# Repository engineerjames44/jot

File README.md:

# Jot

A voice-first personal hub for iOS 26. Hold the mic button, speak, and Jot turns
it into a note, task, reminder, or calendar event.

## Pipeline

```
AudioSource (MicAudioSource; BLE later)
  → SpeechTranscription (SpeechAnalyzer, on-device)
  → OnDeviceClassifier (Apple Foundation Models, default)
    or ProxyClassifier (Claude Haiku 4.5 via jamescronin.dev/api/jot/classify, opt-in)
  → JotItem (SwiftData)
  → ReminderScheduler (local notifications, soonest 64)
```

| Folder | What's there |
| --- | --- |
| `Jot/Audio` | `AudioSource` protocol and the mic implementation |
| `Jot/Speech` | On-device transcription and format conversion |
| `Jot/AI` | Sorting: on-device classifier (default), the jamescronin.dev proxy for Claude (opt-in), prompts and parsing |
| `Jot/Model` | `JotItem` SwiftData model |
| `Jot/Services` | Capture loop, Keychain, notifications, EventKit (read-only) |
| `Jot/Views` | Today, Inbox, item detail, Settings, record button |

### Adding the BLE source

Implement `AudioSource` (return an `AsyncStream<AudioChunk>` of PCM buffers in any
format, finish it on `stop()`) and pass it to `CaptureController(source:)` in
`JotApp`. Transcription converts to the analyzer's format itself.

## Targets

| Target | What it is |
| --- | --- |
| `Jot` | The app |
| `JotWidgets` | Home/Lock Screen widgets, the Control Center control, and the capture Live Activity |

`Shared/` is compiled into both: the SwiftData model, design system, brand colors,
the App Group store, Live Activity attributes, and the record intent. Both targets
use the App Group `group.com.jamescronin.Jot` so they read the same items.

## Develop tab (change notes)

A tab for noting changes to Jot itself as you use it. Tap the orb to record (tap
again to save); the words are kept exactly as said (no Claude), along with the
recording, the screen you were on, and the app version. **Shake the phone
anywhere** to record a note tagged with the current screen. **Export PDF** or
**Export TXT** makes a file of every note (open ones grouped into Bugs, Changes,
and Ideas, then Done) and opens the share sheet: Save to Files, AirDrop, Mail, and so on.

On by default in Debug builds, off in Release; toggle it in Settings › Developer.

## Setup

1. Open `Jot.xcodeproj` in Xcode 26.
2. Pick your team under Signing & Capabilities (and change the bundle ID if needed).
3. Run on a device or simulator. Sorting works out of the box on Apple's on-device model.
   Claude sorting is an opt-in under **Settings**; it goes through the jamescronin.dev proxy,
   which holds the API key, so Release builds never hold a key. Debug builds also accept a personal
   Claude key in Settings (Keychain only) for experiments, which calls Claude directly.

For UI work, launch a Debug build with the argument `-JotSampleData YES`
(Edit Scheme › Run › Arguments) to fill an empty store with a sample day and sample change notes.

The first recording downloads the on-device speech model for your language.
If sorting fails (model unavailable, offline), the transcript is saved as a note and sorted later, so nothing is lost.

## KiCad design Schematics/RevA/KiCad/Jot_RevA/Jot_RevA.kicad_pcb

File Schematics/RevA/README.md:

# Jot Rev A

First custom PCB: handheld push-to-talk voice capture with BLE sync to the iPhone app.
Architecture: [JOT-HW-001](Architecture/JOT-HW-001_Hardware_Architecture.pdf).

| Folder | What goes there |
| --- | --- |
| `Architecture/` | JOT-HW-001 and other design documents (pin map, power budget) |
| `Datasheets/` | Part datasheets, grouped by block from JOT-HW-001 section 4 |
| `KiCad/` | The KiCad project: schematic, PCB, project-local symbols and footprints |
| `BOM/` | Bill of materials exported from KiCad, with LCSC part numbers |
| `Fabrication/` | Gerbers, drill files, and assembly files sent to the board house |

## Datasheets by block

| Folder | Parts |
| --- | --- |
| `Power/` | USB-C connector and ESD, MCP73831 charger, TPS7A02 LDO, MAX17048, JST-PH, battery |
| `MCU/` | Raytac MDBT50Q-1MV2, nRF52840 Product Specification, 32.768 kHz crystal |
| `Audio/` | TDK T3902 PDM microphone, AO3401A mic power switch |
| `Storage/` | 128 MB QSPI NOR flash |
| `Sensors/` | LIS2DW12 accelerometer, DRV2605L haptic driver, LRA |
| `UI/` | Button, RGB LED, Rec LED, charge LED, buzzer, AO3400A, 1N4148W |
| `NFC/` | NFC antenna design notes and tuning references |
| `Passives/` | Samsung CL05/CL10 capacitor and UNI-ROYAL resistor series datasheets |

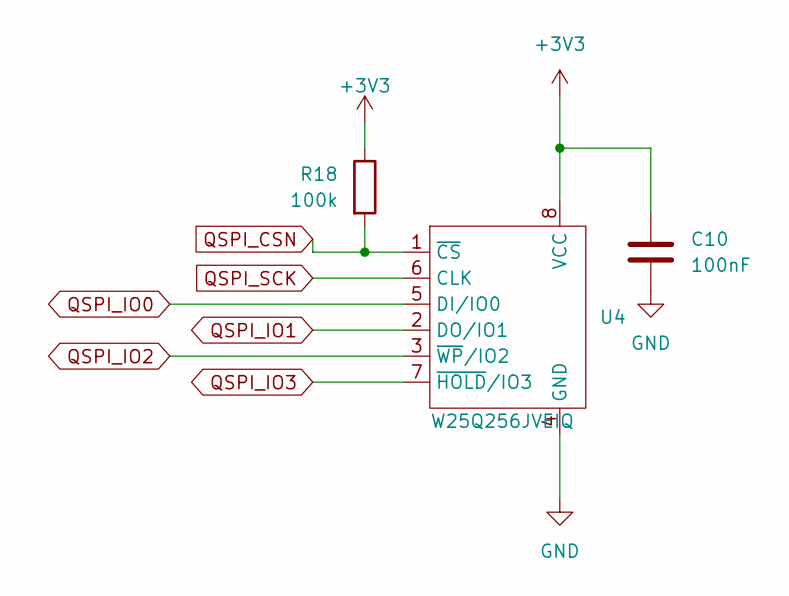
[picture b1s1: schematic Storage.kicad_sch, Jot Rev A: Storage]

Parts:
C10: 100nF; C_0402_1005Metric
R18: 100k; R_0402_1005Metric
U4: W25Q256JVEIQ; WSON-8-1EP_8x6mm_P1.27mm_EP3.4x4.3mm

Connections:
+3V3: C10.1, R18.1, U4.8 (VCC); also elsewhere on the board
GND: C10.2, U4.4 (GND); also elsewhere on the board
QSPI_CSN: R18.2, U4.1 (~CS); also elsewhere on the board
QSPI_IO0: U4.5 (DI/IO0); also elsewhere on the board
QSPI_IO1: U4.2 (DO/IO1); also elsewhere on the board
QSPI_IO2: U4.3 (~WP/IO2); also elsewhere on the board
QSPI_IO3: U4.7 (~HOLD/IO3); also elsewhere on the board
QSPI_SCK: U4.6 (CLK); also elsewhere on the board

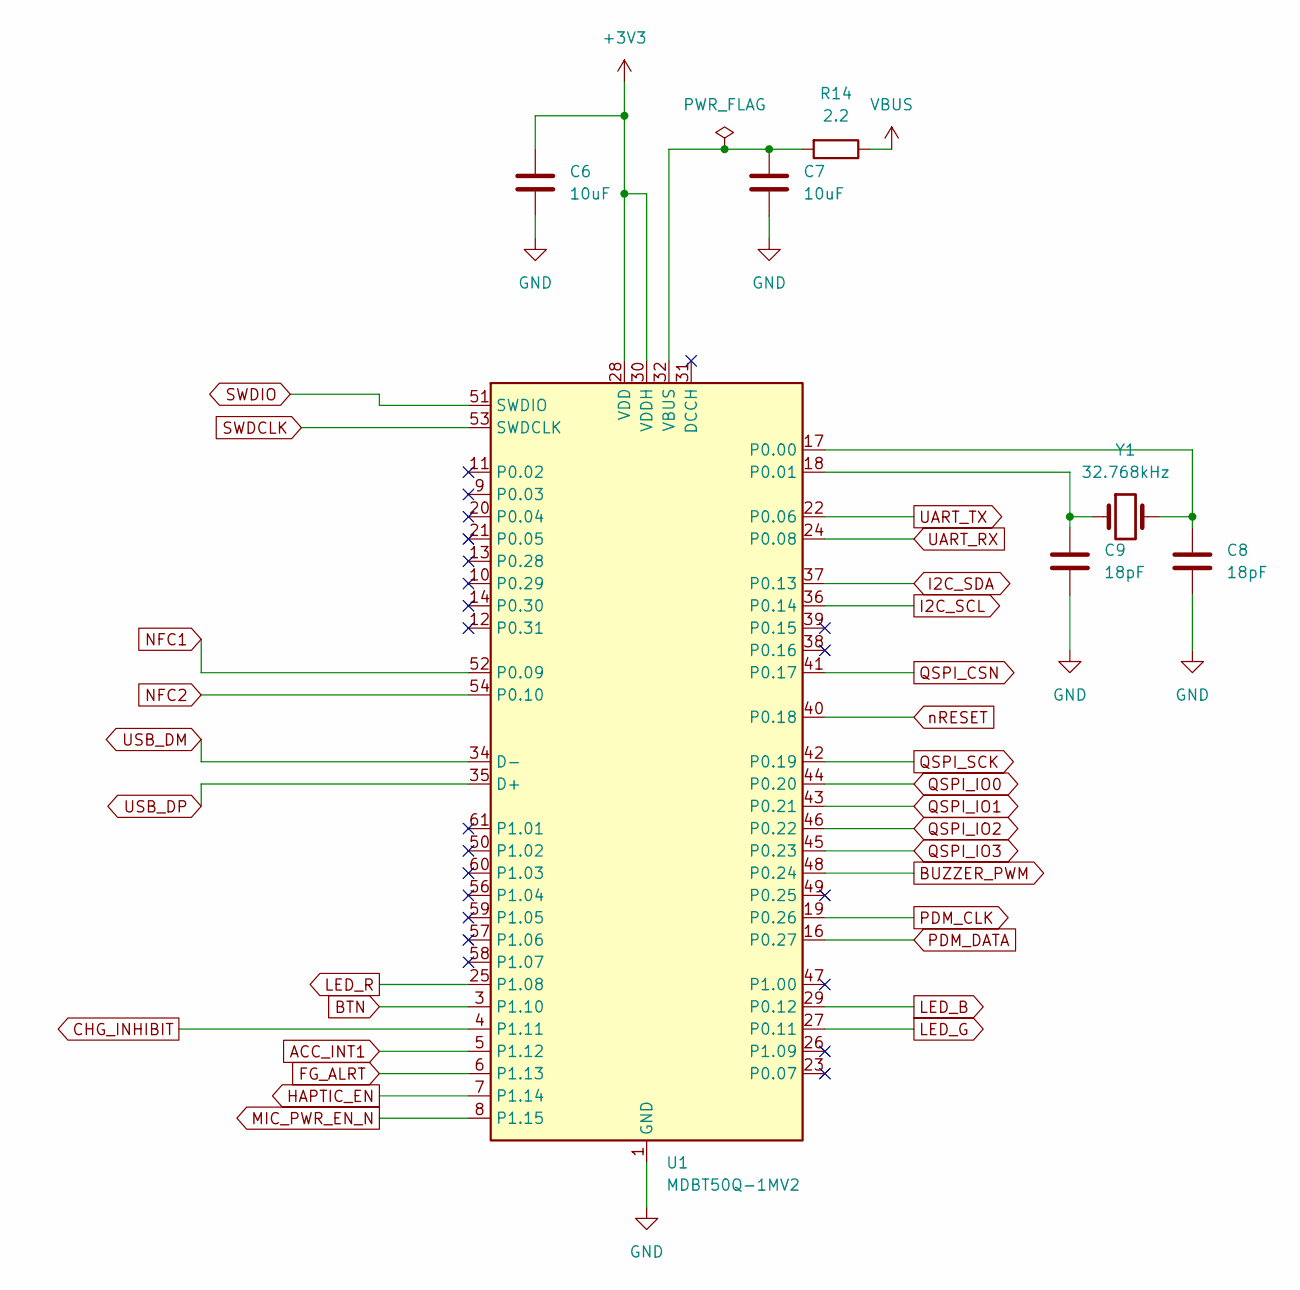
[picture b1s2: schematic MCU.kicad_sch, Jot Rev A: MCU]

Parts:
C6, C7: 10uF; C_0603_1608Metric
C8, C9: 18pF; C_0402_1005Metric
R14: 2.2; R_0402_1005Metric
U1: MDBT50Q-1MV2; Raytac_MDBT50Q
Y1: 32.768kHz; Crystal_SMD_3215-2Pin_3.2x1.5mm

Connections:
+3V3: C6.1, U1.28 (VDD), U1.30 (VDDH); also elsewhere on the board
ACC_INT1: U1.5 (P1.12); also elsewhere on the board
BTN: U1.3 (P1.10); also elsewhere on the board
BUZZER_PWM: U1.48 (P0.24); also elsewhere on the board
CHG_INHIBIT: U1.4 (P1.11); also elsewhere on the board
FG_ALRT: U1.6 (P1.13); also elsewhere on the board
GND: C6.2, C7.2, C8.2, C9.2, U1.1 (GND), U1.2 (GND), U1.15 (GND), U1.33 (GND), U1.55 (GND); also elsewhere on the board
HAPTIC_EN: U1.7 (P1.14); also elsewhere on the board
I2C_SCL: U1.36 (P0.14); also elsewhere on the board
I2C_SDA: U1.37 (P0.13); also elsewhere on the board
LED_B: U1.29 (P0.12); also elsewhere on the board
LED_G: U1.27 (P0.11); also elsewhere on the board
LED_R: U1.25 (P1.08); also elsewhere on the board
MIC_PWR_EN_N: U1.8 (P1.15); also elsewhere on the board
NFC1: U1.52 (P0.09); also elsewhere on the board
NFC2: U1.54 (P0.10); also elsewhere on the board
unnamed: C8.1, U1.17 (P0.00), Y1.2
unnamed: C9.1, U1.18 (P0.01), Y1.1
unnamed: C7.1, R14.2, U1.32 (VBUS)
PDM_CLK: U1.19 (P0.26); also elsewhere on the board
PDM_DATA: U1.16 (P0.27); also elsewhere on the board
QSPI_CSN: U1.41 (P0.17); also elsewhere on the board
QSPI_IO0: U1.44 (P0.20); also elsewhere on the board
QSPI_IO1: U1.43 (P0.21); also elsewhere on the board
QSPI_IO2: U1.46 (P0.22); also elsewhere on the board
QSPI_IO3: U1.45 (P0.23); also elsewhere on the board
QSPI_SCK: U1.42 (P0.19); also elsewhere on the board
SWDCLK: U1.53 (SWDCLK); also elsewhere on the board
SWDIO: U1.51 (SWDIO); also elsewhere on the board
UART_RX: U1.24 (P0.08); also elsewhere on the board
UART_TX: U1.22 (P0.06); also elsewhere on the board
USB_DM: U1.34 (D-); also elsewhere on the board
USB_DP: U1.35 (D+); also elsewhere on the board
VBUS: R14.1; also elsewhere on the board
nRESET: U1.40 (P0.18); also elsewhere on the board

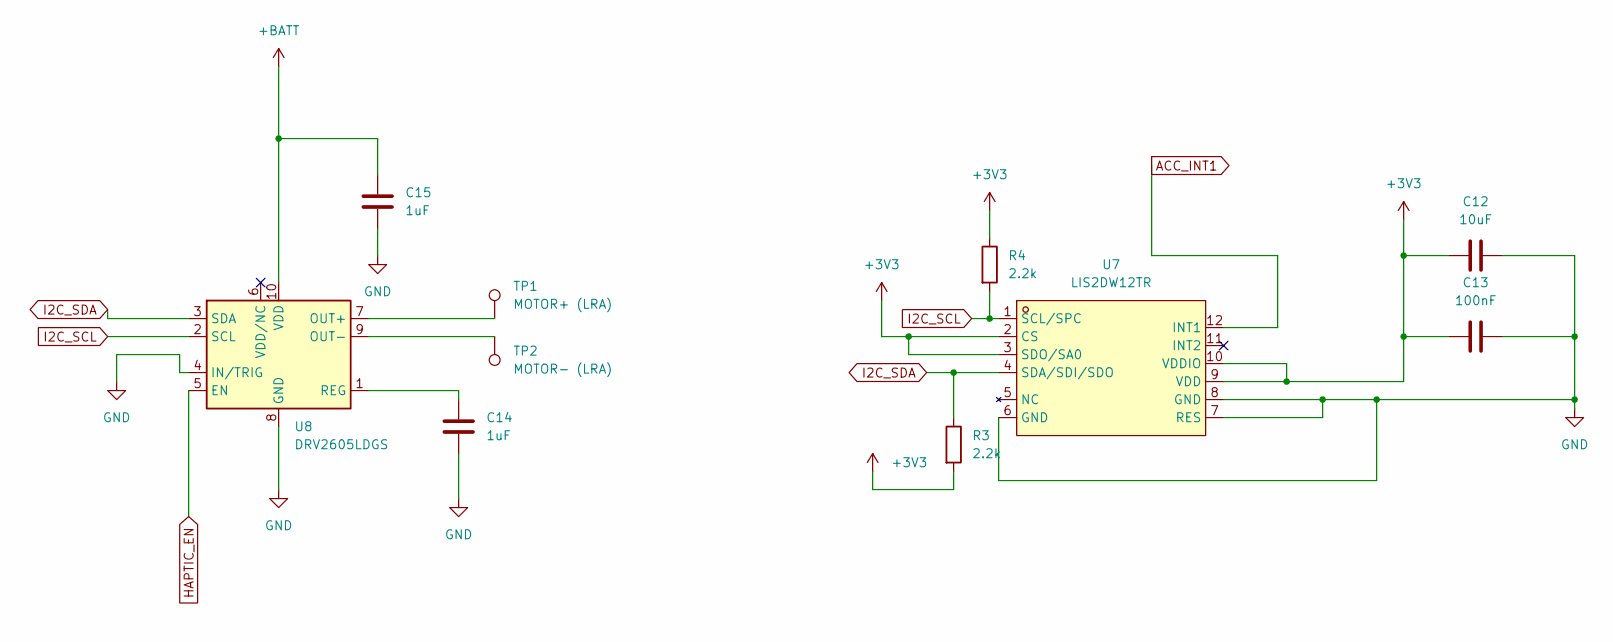
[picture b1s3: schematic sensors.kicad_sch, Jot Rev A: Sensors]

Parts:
C12: 10uF; C_0603_1608Metric
C13: 100nF; C_0402_1005Metric
C14, C15: 1uF; C_0402_1005Metric
R3, R4: 2.2k; R_0402_1005Metric
TP1: MOTOR+ (LRA); TestPoint_Pad_D2.0mm
TP2: MOTOR- (LRA); TestPoint_Pad_D2.0mm
U7: LIS2DW12TR; LGA-12_2x2mm_P0.5mm; MPN LIS2DW12TR; LCSC Part C189624
U8: DRV2605LDGS; TSSOP-10_3x3mm_P0.5mm

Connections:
+3V3: C12.2, C13.2, R3.2, R4.1, U7.2 (CS), U7.3 (SDO/SA0), U7.9 (VDD), U7.10 (VDDIO); also elsewhere on the board
+BATT: C15.1, U8.10 (VDD); also elsewhere on the board
ACC_INT1: U7.12 (INT1); also elsewhere on the board
GND: C12.1, C13.1, C14.2, C15.2, U7.6 (GND), U7.7 (RES), U7.8 (GND), U8.4 (IN/TRIG), U8.8 (GND); also elsewhere on the board
HAPTIC_EN: U8.5 (EN); also elsewhere on the board
I2C_SCL: R4.2, U7.1 (SCL/SPC), U8.2 (SCL); also elsewhere on the board
I2C_SDA: R3.1, U7.4 (SDA/SDI/SDO), U8.3 (SDA); also elsewhere on the board
unnamed: TP1.1 (1_1), U8.7 (OUT+)
unnamed: TP2.1 (1_1), U8.9 (OUT-)
unnamed: C14.1, U8.1 (REG)

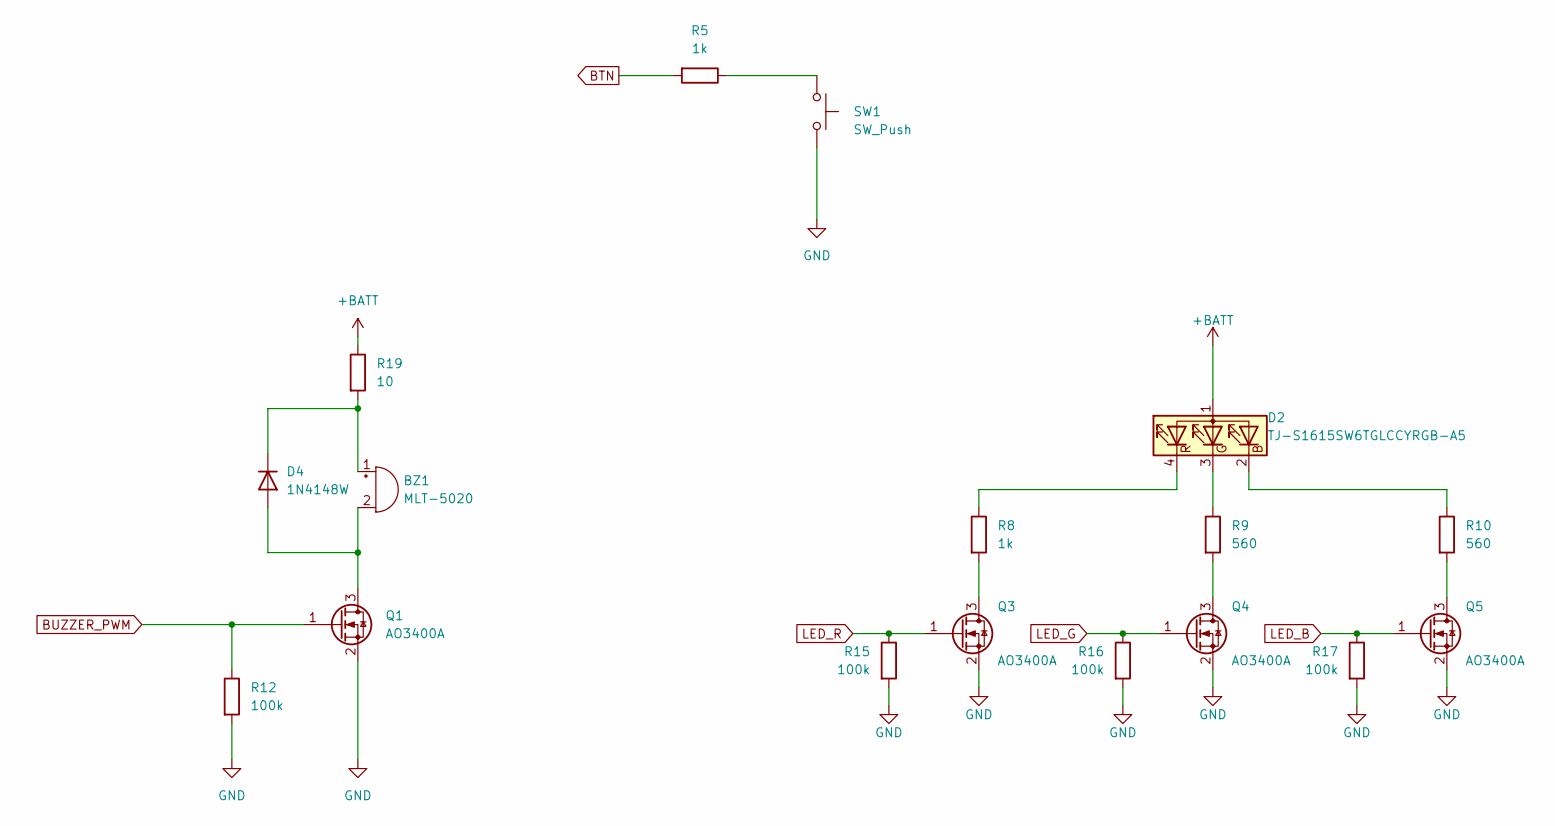
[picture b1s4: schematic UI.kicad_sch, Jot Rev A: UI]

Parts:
BZ1: MLT-5020; BUZ-SMD_L5.0-W5.5-P4.60
D2: TJ-S1615SW6TGLCCYRGB-A5; LED_RGB_TOGIALED_1615_1.6x1.5mm
D4: 1N4148W; D_SOD-123
Q1, Q3, Q4, Q5: AO3400A; SOT-23
R5, R8: 1k; R_0402_1005Metric
R9, R10: 560; R_0402_1005Metric
R12, R15, R16, R17: 100k; R_0402_1005Metric
R19: 10; R_2512_6332Metric
SW1: SW_Push; KEY-SMD_TX-1010-X-X

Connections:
+BATT: D2.1 (A), R19.1; also elsewhere on the board
BTN: R5.2; also elsewhere on the board
BUZZER_PWM: Q1.1 (G), R12.1; also elsewhere on the board
GND: Q1.2 (S), Q3.2 (S), Q4.2 (S), Q5.2 (S), R12.2, R15.2, R16.2, R17.2, SW1.2; also elsewhere on the board
LED_B: Q5.1 (G), R17.1; also elsewhere on the board
LED_G: Q4.1 (G), R16.1; also elsewhere on the board
LED_R: Q3.1 (G), R15.1; also elsewhere on the board
unnamed: BZ1.1 (+), D4.1 (K), R19.2
unnamed: BZ1.2 (-), D4.2 (A), Q1.3 (D)
unnamed: D2.2 (BK), R10.1
unnamed: D2.3 (GK), R9.1
unnamed: D2.4 (RK), R8.1
unnamed: Q3.3 (D), R8.2
unnamed: Q4.3 (D), R9.2
unnamed: Q5.3 (D), R10.2
unnamed: R5.1, SW1.1

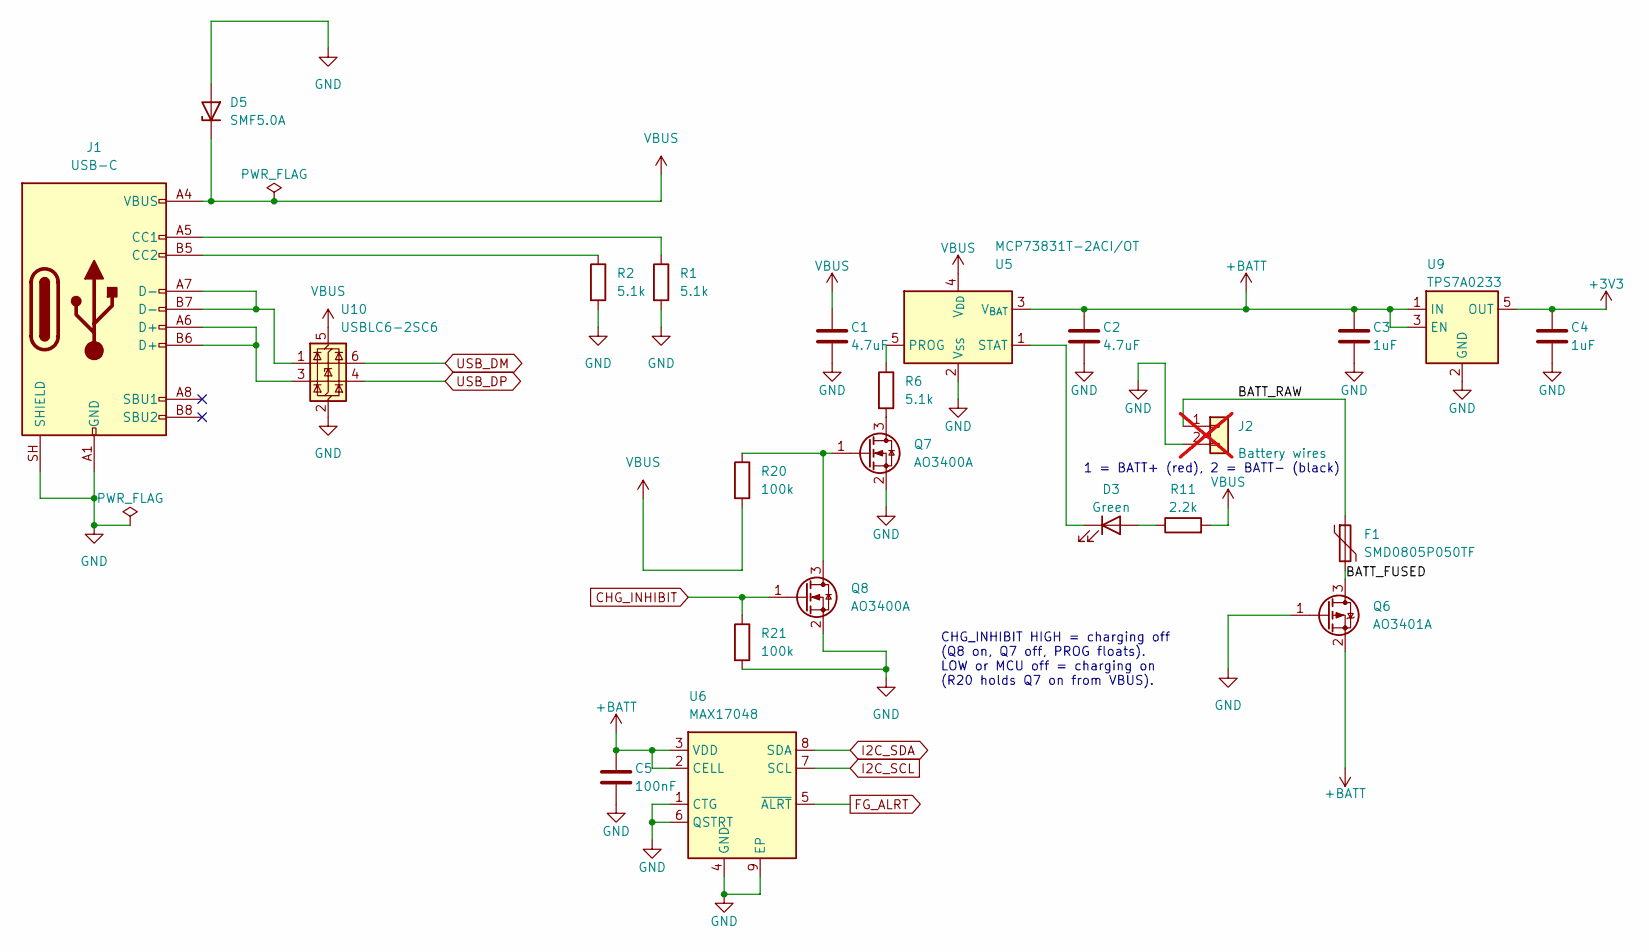
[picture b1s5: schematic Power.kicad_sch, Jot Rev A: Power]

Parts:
C1, C2: 4.7uF; C_0402_1005Metric
C3, C4: 1uF; C_0402_1005Metric
C5: 100nF; C_0402_1005Metric
D3: Green; LED_0603_1608Metric; LCSC C7429914
D5: SMF5.0A; D_SOD-123F
F1: SMD0805P050TF; Fuse_0805_2012Metric
J1: USB-C; USB_C_Receptacle_HRO_TYPE-C-31-M-12
J2: Battery wires; SolderWire-0.15sqmm_1x02_P4mm_D0.5mm_OD1.5mm; not fitted
Q6: AO3401A; SOT-23
Q7, Q8: AO3400A; SOT-23
R1, R2, R6: 5.1k; R_0402_1005Metric
R11: 2.2k; R_0402_1005Metric; LCSC C25879
R20, R21: 100k; R_0402_1005Metric
U5: MCP73831T-2ACI/OT; SOT-23-5
U6: MAX17048; DFN-8-1EP_2x2mm_P0.5mm_EP0.9x1.3mm; LCSC C2682616
U9: TPS7A0233; SOT-23-5; LCSC C2887324
U10: USBLC6-2SC6; SOT-23-6

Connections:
+3V3: C4.1, U9.5 (OUT); also elsewhere on the board
+BATT: C2.1, C3.1, C5.1, Q6.2 (S), U5.3 (V_{BAT}), U6.2 (CELL), U6.3 (VDD), U9.1 (IN), U9.3 (EN); also elsewhere on the board
/Power/BATT_FUSED: F1.2, Q6.3 (D)
/Power/BATT_RAW: F1.1, J2.1
CHG_INHIBIT: Q8.1 (G), R21.1; also elsewhere on the board
FG_ALRT: U6.5 (~ALRT); also elsewhere on the board
GND: C1.2, C2.2, C3.2, C4.2, C5.2, D5.2 (A), J1.A1 (GND), J1.A12 (GND), J1.B1 (GND), J1.B12 (GND), J1.SH (SHIELD), J2.2, Q6.1 (G), Q7.2 (S), Q8.2 (S), R1.2, R2.2, R21.2, U5.2 (V_{SS}), U6.1 (CTG), U6.4 (GND), U6.6 (QSTRT), U6.9 (EP), U9.2 (GND), U10.2 (GND); also elsewhere on the board
I2C_SCL: U6.7 (SCL); also elsewhere on the board
I2C_SDA: U6.8 (SDA); also elsewhere on the board
unnamed: D3.2 (A), R11.1
unnamed: D3.1 (K), U5.1 (STAT)
unnamed: J1.A5 (CC1), R1.1
unnamed: J1.B5 (CC2), R2.1
unnamed: J1.A6 (D+), J1.B6 (D+), U10.3 (I/O2)
unnamed: J1.A7 (D-), J1.B7 (D-), U10.1 (I/O1)
unnamed: Q7.3 (D), R6.2
unnamed: Q7.1 (G), Q8.3 (D), R20.1
unnamed: R6.1, U5.5 (PROG)
USB_DM: U10.6 (I/O1); also elsewhere on the board
USB_DP: U10.4 (I/O2); also elsewhere on the board
VBUS: C1.1, D5.1 (K), J1.A4 (VBUS), J1.A9 (VBUS), J1.B4 (VBUS), J1.B9 (VBUS), R11.2, R20.2, U5.4 (V_{DD}), U10.5 (VBUS); also elsewhere on the board

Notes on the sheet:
CHG_INHIBIT HIGH = charging off (Q8 on, Q7 off, PROG floats). LOW or MCU off = charging on (R20 holds Q7 on from VBUS).
1 = BATT+ (red), 2 = BATT− (black)

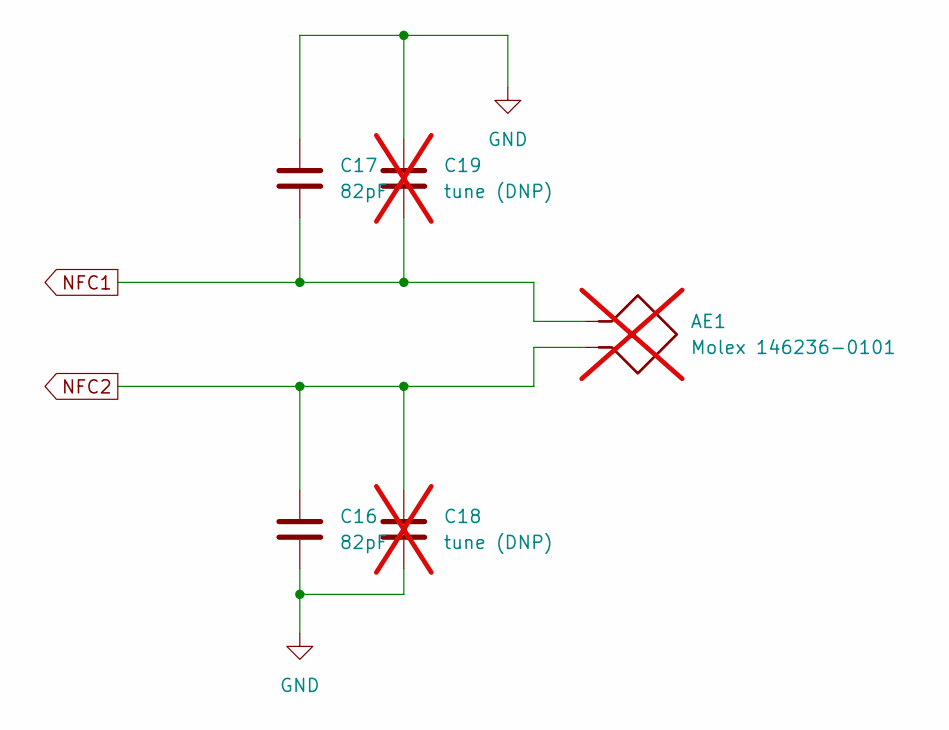
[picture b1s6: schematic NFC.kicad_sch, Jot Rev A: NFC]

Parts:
AE1: Molex 146236-0101; SolderWire-0.1sqmm_1x02_P3.6mm_D0.4mm_OD1mm; not fitted
C16, C17: 82pF; C_0402_1005Metric
C18, C19: tune (DNP); C_0402_1005Metric; not fitted

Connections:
GND: C16.2, C17.1, C18.2, C19.1; also elsewhere on the board
NFC1: AE1.1, C17.2, C19.2; also elsewhere on the board
NFC2: AE1.2, C16.1, C18.1; also elsewhere on the board

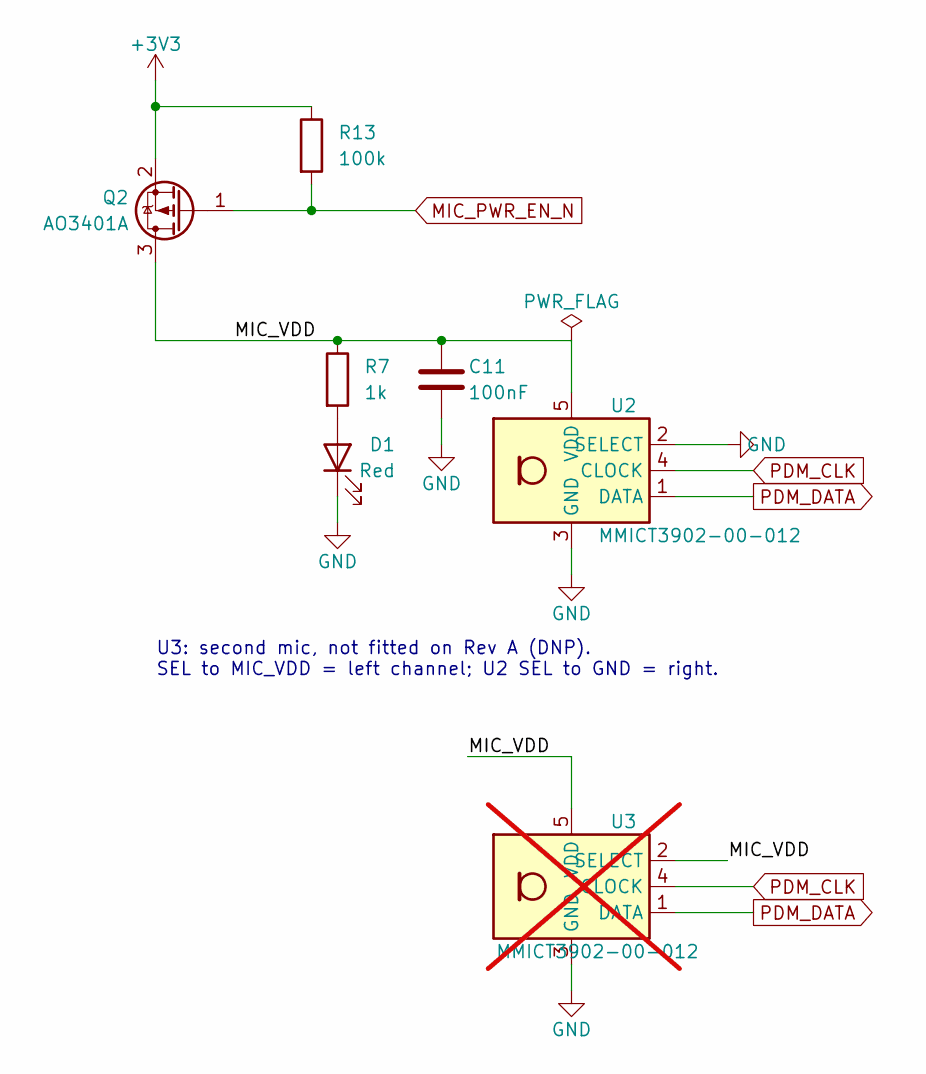
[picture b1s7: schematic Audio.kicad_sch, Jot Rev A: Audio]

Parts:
C11: 100nF; C_0402_1005Metric
D1: Red; LED_0603_1608Metric
Q2: AO3401A; SOT-23
R7: 1k; R_0402_1005Metric
R13: 100k; R_0402_1005Metric
U2: MMICT3902-00-012; Knowles_LGA-5_3.5x2.65mm
U3: MMICT3902-00-012; Knowles_LGA-5_3.5x2.65mm; not fitted

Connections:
+3V3: Q2.2 (S), R13.1; also elsewhere on the board
/Audio/MIC_VDD: C11.1, Q2.3 (D), R7.1, U2.5 (VDD), U3.2 (SELECT), U3.5 (VDD)
GND: C11.2, D1.1 (K), U2.2 (SELECT), U2.3 (GND), U3.3 (GND); also elsewhere on the board
MIC_PWR_EN_N: Q2.1 (G), R13.2; also elsewhere on the board
unnamed: D1.2 (A), R7.2
PDM_CLK: U2.4 (CLOCK), U3.4 (CLOCK); also elsewhere on the board
PDM_DATA: U2.1 (DATA), U3.1 (DATA); also elsewhere on the board

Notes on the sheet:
U3: second mic, not fitted on Rev A (DNP). SEL to MIC_VDD = left channel; U2 SEL to GND = right.

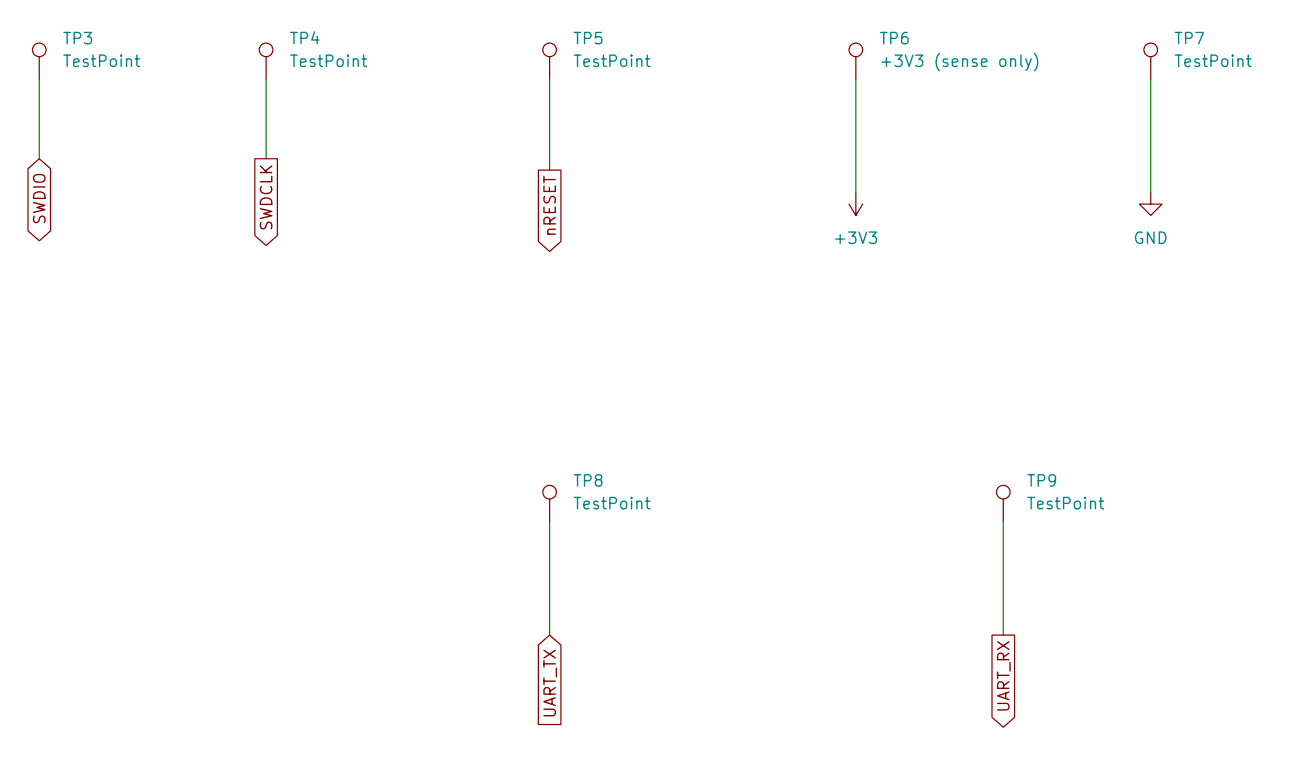
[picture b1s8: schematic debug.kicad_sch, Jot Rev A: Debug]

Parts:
TP3, TP4, TP5, TP7, TP8, TP9: TestPoint; TestPoint_Pad_D1.0mm
TP6: +3V3 (sense only); TestPoint_Pad_D1.0mm

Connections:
+3V3: TP6.1 (1_1); also elsewhere on the board
GND: TP7.1 (1_1); also elsewhere on the board
SWDCLK: TP4.1 (1_1); also elsewhere on the board
SWDIO: TP3.1 (1_1); also elsewhere on the board
UART_RX: TP9.1 (1_1); also elsewhere on the board
UART_TX: TP8.1 (1_1); also elsewhere on the board
nRESET: TP5.1 (1_1); also elsewhere on the board

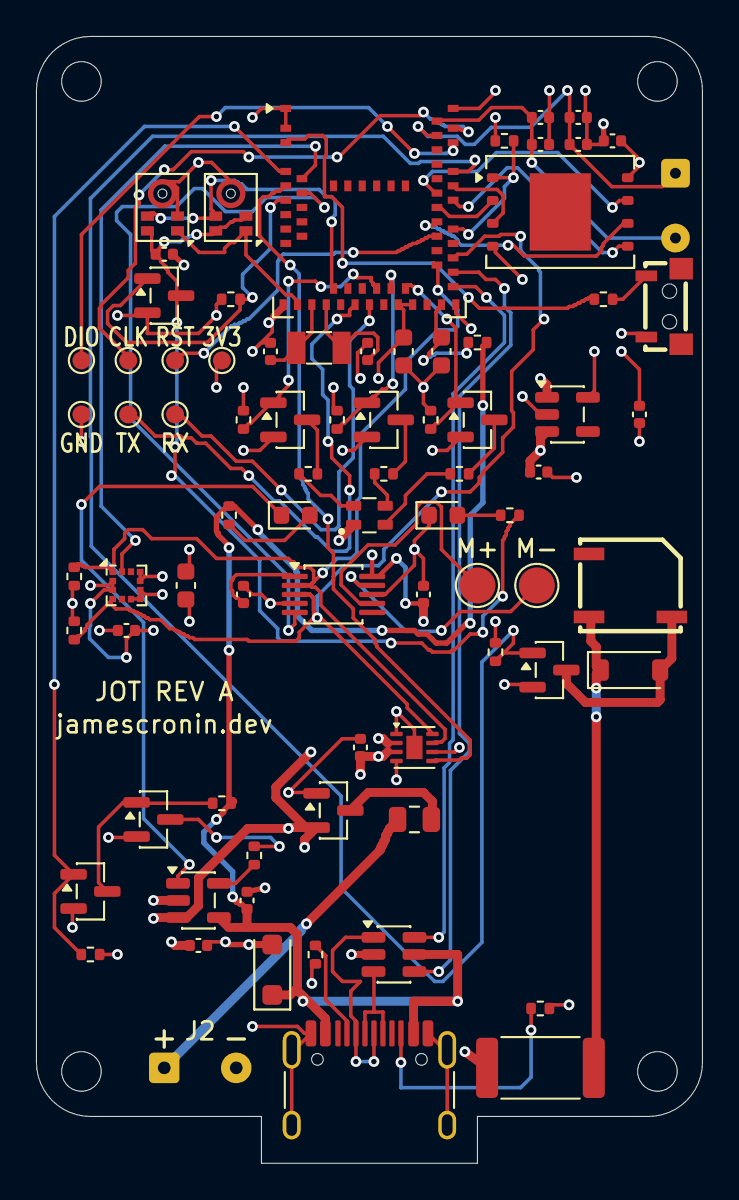
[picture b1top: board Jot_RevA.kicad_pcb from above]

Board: 4 copper layers, 37.0 x 62.6 mm, 83 parts (0 on the bottom side), 61 nets.

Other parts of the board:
H1, H2, H3, H4: MountingHole_2.2mm_M2

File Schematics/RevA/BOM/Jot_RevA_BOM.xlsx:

Quantity | Manufacture Part Number | Manufacturer | LCSC Part Number | Designator | Description
1 | MMICT3902-00-012 | TDK InvenSense | C3171752 | U2 | PDM MEMS mic, bottom port
1 | W25Q256JVEIQ | Winbond | C97522 | U4 | 256 Mbit (32 MB) QSPI NOR flash, WSON-8 8x6 mm (about 68 min of 8 KB/s audio)
1 | MCP73831T-2ACI/OT | Microchip | C424093 | U5 | 1-cell LiPo charger, 4.2 V, tri-state STAT, SOT-23-5
1 | MAX17048G+T10 | Maxim / ADI | C2682616 | U6 | Fuel gauge, DFN-8 2x2
1 | LIS2DW12TR | STMicroelectronics | C189624 | U7 | Accelerometer, LGA-12 2x2
1 | DRV2605LDGSR | Texas Instruments | C527464 | U8 | Haptic driver, VSSOP-10 (pre-ordered at JLCPCB 8 Oct: low stock)
1 | TPS7A0233PDBVR | Texas Instruments | C2887324 | U9 | 3.3 V LDO, 200 mA, 25 nA Iq, SOT-23-5
1 | USBLC6-2SC6 | STMicroelectronics | C7519 | U10 | USB ESD protection, SOT-23-6
2 | AO3401A | UMW | C347476 | Q2,Q6 | P-MOSFET, SOT-23: mic + Rec LED power switch (Q2); battery reverse-polarity pro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
6 | AO3400A | AOS | C20917 | Q1,Q3,Q4,Q5,Q7,Q8 | N-MOSFET, SOT-23: buzzer driver (Q1), RGB cathode switches (Q3-Q5), charge inhi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
1 | 1N4148W | ST(Semtech) | C81598 | D4 | Buzzer flyback diode, SOD-123
1 | TYPE-C-31-M-12 | Korean Hroparts | C165948 | J1 | USB-C receptacle, 16-pin
1 | TS-1010-C-A | - | C692458 | SW1 | Side-push tactile switch, SMD right angle, 4.7x2.3 mm
1 | MLT-5020 | Huaneng | C94598 | BZ1 | Magnetic buzzer, 4 kHz, 5x5 mm
1 | SC-32S 32.768kHz 20PPM 12.5pF | Seiko | C97606 | Y1 | 32.768 kHz crystal, 3215, 12.5 pF
1 | KT-0603R | Hubei KENTO | C2286 | D1 | Red LED 0603 (Rec)
1 | TJ-S1615SW6TGLCCYRGB-A5 | TOGIALED | C273610 | D2 | RGB LED common anode, 1.6x1.5 mm (pin 1 anode; 2 B, 3 G, 4 R cathodes)
1 | NCD0603G3 | NationStar | C7429914 | D3 | Green LED 0603 (charge)
3 | 0402WGF5101TCE | UNI-ROYAL | C25905 | R1,R2,R6 | 5.1k 1% 0402 (USB-C CC; charger PROG: 1000 V / 5.1k = 196 mA)
2 | CL05A475KP5NRNC | Samsung | C368809 | C1,C2 | 4.7 uF 10 V X5R 0402 (charger VDD and VBAT; MCP73831 needs at least 4.7 uF on e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
3 | 0402WGF1001TCE | UNI-ROYAL | C11702 | R5,R7,R8 | 1k 1% 0402 (R5 BTN series ESD resistor; Rec LED; RGB red)
2 | 0402WGF5600TCE | UNI-ROYAL | C25126 | R9,R10 | 560R 1% 0402 (RGB green, blue)
3 | 0402WGF2201TCE | UNI-ROYAL | C25879 | R3,R4,R11 | 2.2k 1% 0402 (I2C pull-ups R3/R4: MAX17048 60 pF + 300 ns rise; charge LED R11)
8 | 0402WGF1003TCE | UNI-ROYAL | C25741 | R12,R13,R15,R16,R17,R18,R20,R21 | 100k 1% 0402 (Q1, Q3-Q5 gate pull-downs; Q2 gate pull-up; U4 /CS pull-up; R20 Q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
1 | 0402WGJ022JTCE | UNI-ROYAL | C25158 | R14 | 2.2R 5% 0402 (U1 VBUS series, Nordic ref)
4 | CL05B104KO5NNNC | Samsung | C1525 | C5,C10,C11,C13 | 100 nF 16 V X7R 0402 decoupling
4 | CL05A105KA5NQNC | Samsung | C52923 | C3,C4,C14,C15 | 1 uF 25 V X5R 0402 (U9 LDO in/out; U8 REG and VDD)
3 | CL10A106KP8NNNC | Samsung | C19702 | C6,C7,C12 | 10 uF 10 V X5R 0603 (U1 VDD/VDDH and VBUS, Raytac ref 8.3; U7 accelerometer)
2 | CL05C180JB5NNNC | Samsung | C307443 | C8,C9 | 18 pF C0G 0402 (32.768 kHz load caps; checked against nRF52840 PS)
2 | CC0402JRNPO9BN820 | YAGEO | C107011 | C16,C17 | 82 pF 5% NP0 50 V 0402 (NFC tuning for the Molex 146236-0101 antenna, 3.1 uH; N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
1 | 25121WF100JT4E | UNI-ROYAL | C47019 | R19 | 10R 1% 2512, 1 W (buzzer series resistor; survives a stuck-on Q1: 0.49 W)
1 | MDBT50Q-1MV2 | Raytac | C5118826 | U1 | nRF52840 module, chip antenna (pre-ordered at JLCPCB 8 Oct, held in My Parts)
1 | SMD0805P050TF | RUILON | C20978 | F1 | Polyfuse 0.5 A hold / 1 A trip, 6 V, 0805 (battery rail; 0.33 A hold at 60 C)
1 | SMF5.0A | MDD | C193402 | D5 | TVS 5 V standoff, 6.4-7 V breakdown, unidirectional, SOD-123FL (VBUS hot-plug; 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
Quantities are per board. LCSC rounds up to each part's minimum order. Blank LC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
